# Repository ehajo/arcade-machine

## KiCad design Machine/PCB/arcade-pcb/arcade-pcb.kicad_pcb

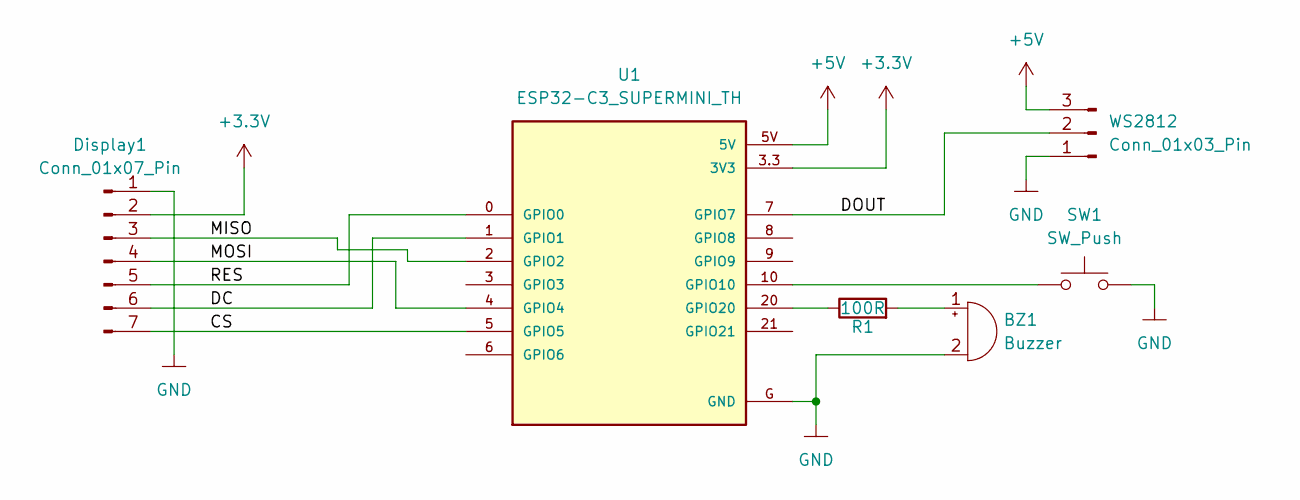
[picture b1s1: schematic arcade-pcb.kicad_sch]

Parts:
BZ1: Buzzer; Buzzer_12x9.5RM7.6
Display1: Conn_01x07_Pin; PinHeader_1x07_P1.27mm_Vertical_hand
R1: 100R; R_Axial_DIN0207_L6.3mm_D2.5mm_P7.62mm_Horizontal
SW1: SW_Push; SW_Tactile_SPST_Angled_PTS645Vx39-2LFS
U1: ESP32-C3_SUPERMINI_TH; MODULE_ESP32-C3_SUPERMINI_SMD
WS2812: Conn_01x03_Pin; PinHeader_1x03_P2.54mm_Vertical

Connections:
+3.3V: Display1.2, U1.3.3 (3V3)
+5V: U1.5V, WS2812.3
/CS: Display1.7, U1.5 (GPIO5)
/DC: Display1.6, U1.1 (GPIO1)
/DOUT: U1.7 (GPIO7), WS2812.2
/MISO: Display1.3, U1.2 (GPIO2)
/MOSI: Display1.4, U1.4 (GPIO4)
/RES: Display1.5, U1.0 (GPIO0)
GND: BZ1.2 (-), Display1.1, SW1.2, U1.G (GND), WS2812.1
unnamed: BZ1.1 (+), R1.2
unnamed: SW1.1, U1.10 (GPIO10)
unnamed: R1.1, U1.20 (GPIO20)

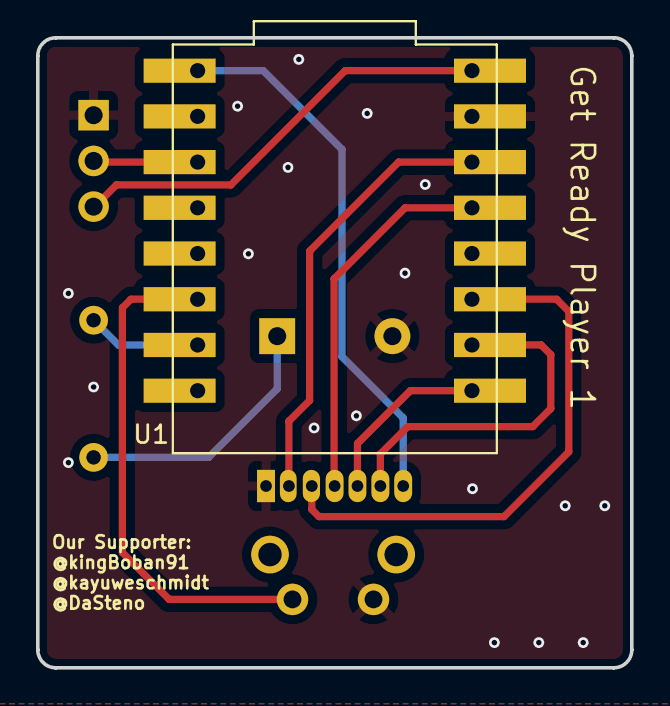
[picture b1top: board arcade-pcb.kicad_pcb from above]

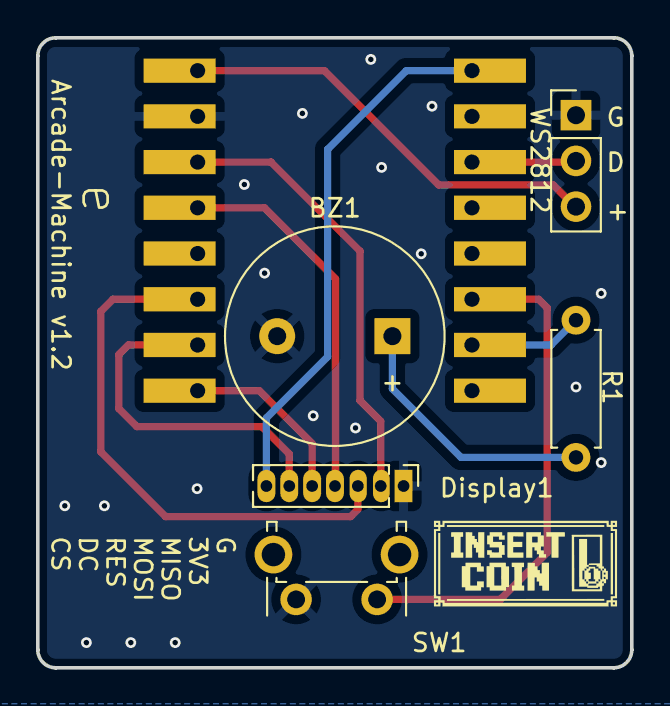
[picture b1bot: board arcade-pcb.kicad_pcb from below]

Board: 2 copper layers, 33.0 x 35.0 mm, 6 parts (5 on the bottom side), 12 nets.

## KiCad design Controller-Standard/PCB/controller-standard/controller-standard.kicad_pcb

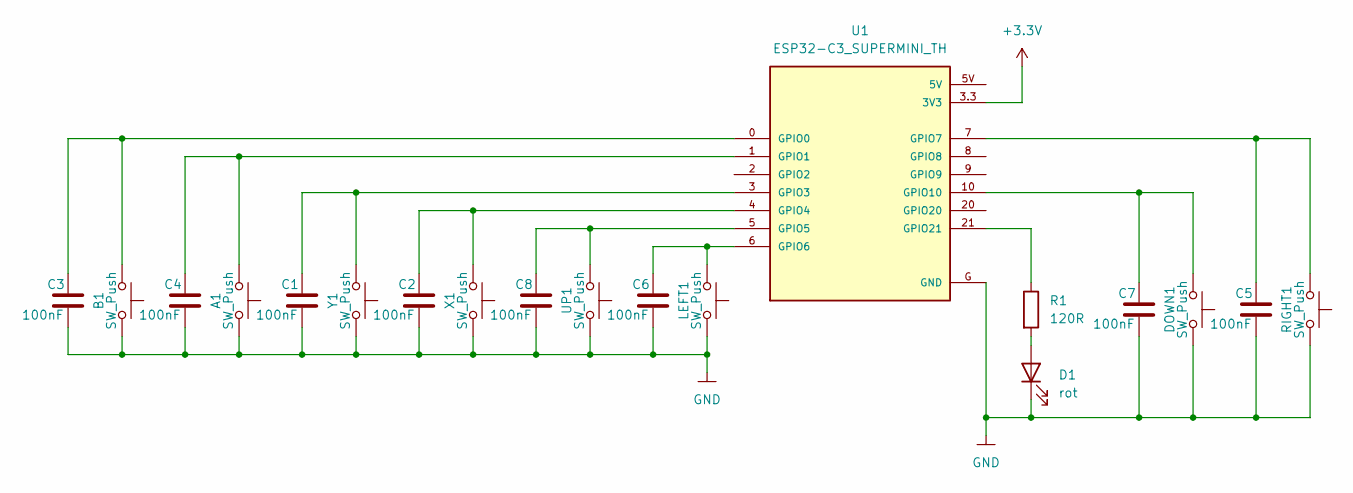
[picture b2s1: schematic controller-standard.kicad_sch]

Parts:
A1: SW_Push; SW_PUSH_6mm_H5mm
B1: SW_Push; SW_PUSH_6mm_H5mm
C1, C2, C3, C4, C5, C6, C7, C8: 100nF; C_0805_2012Metric_Pad1.18x1.45mm_HandSolder
D1: rot; LED_D3.0mm
DOWN1: SW_Push; SW_PUSH_6mm_H5mm
LEFT1: SW_Push; SW_PUSH_6mm_H5mm
R1: 120R; R_Axial_DIN0207_L6.3mm_D2.5mm_P7.62mm_Horizontal
RIGHT1: SW_Push; SW_PUSH_6mm_H5mm
U1: ESP32-C3_SUPERMINI_TH; MODULE_ESP32-C3_SUPERMINI_SMD
UP1: SW_Push; SW_PUSH_6mm_H5mm
X1: SW_Push; SW_PUSH_6mm_H5mm
Y1: SW_Push; SW_PUSH_6mm_H5mm

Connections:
+3.3V: U1.3.3 (3V3)
GND: A1.2, B1.2, C1.2, C2.2, C3.2, C4.2, C5.2, C6.2, C7.2, C8.2, D1.1 (K), DOWN1.2, LEFT1.2, RIGHT1.2, U1.G (GND), UP1.2, X1.2, Y1.2
unnamed: D1.2 (A), R1.2
unnamed: B1.1, C3.1, U1.0 (GPIO0)
unnamed: A1.1, C4.1, U1.1 (GPIO1)
unnamed: C1.1, U1.3 (GPIO3), Y1.1
unnamed: C2.1, U1.4 (GPIO4), X1.1
unnamed: C8.1, U1.5 (GPIO5), UP1.1
unnamed: C6.1, LEFT1.1, U1.6 (GPIO6)
unnamed: C5.1, RIGHT1.1, U1.7 (GPIO7)
unnamed: C7.1, DOWN1.1, U1.10 (GPIO10)
unnamed: R1.1, U1.21 (GPIO21)

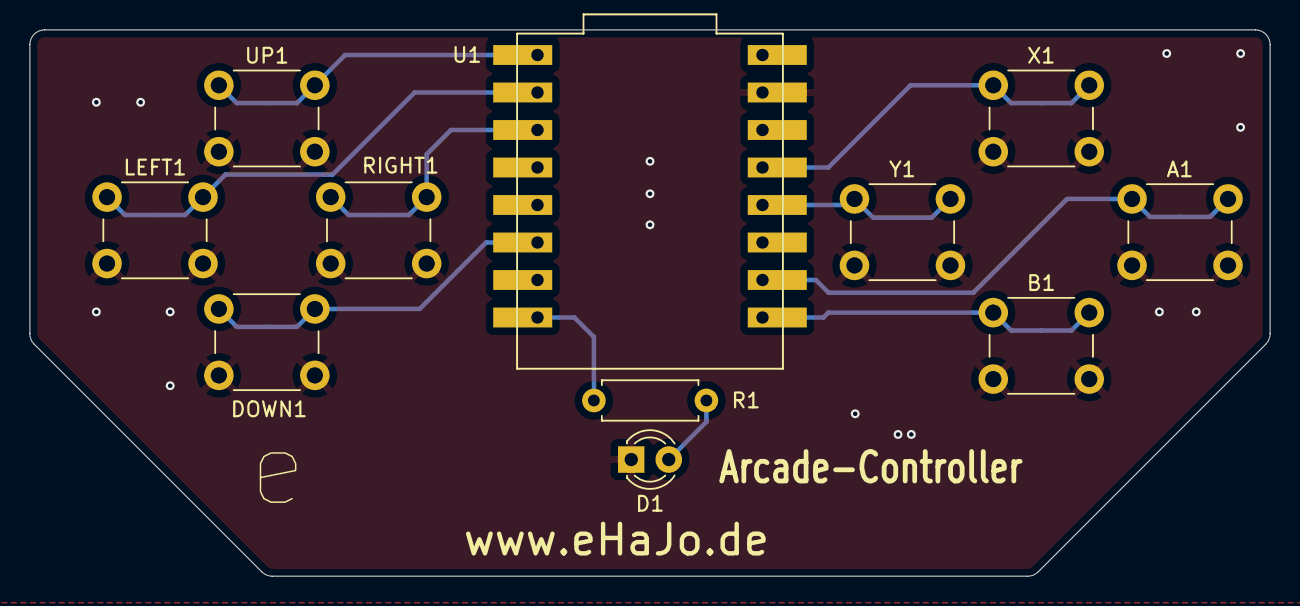
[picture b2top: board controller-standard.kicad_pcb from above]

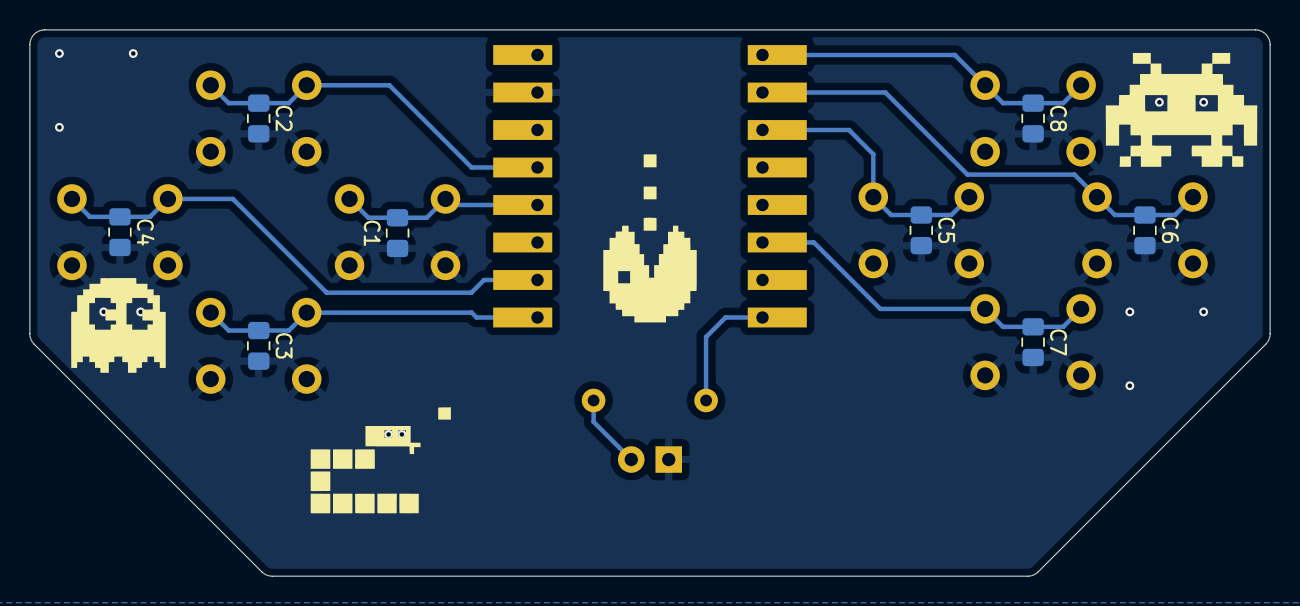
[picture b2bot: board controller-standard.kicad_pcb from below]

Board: 2 copper layers, 84.0 x 37.0 mm, 19 parts (8 on the bottom side), 11 nets.

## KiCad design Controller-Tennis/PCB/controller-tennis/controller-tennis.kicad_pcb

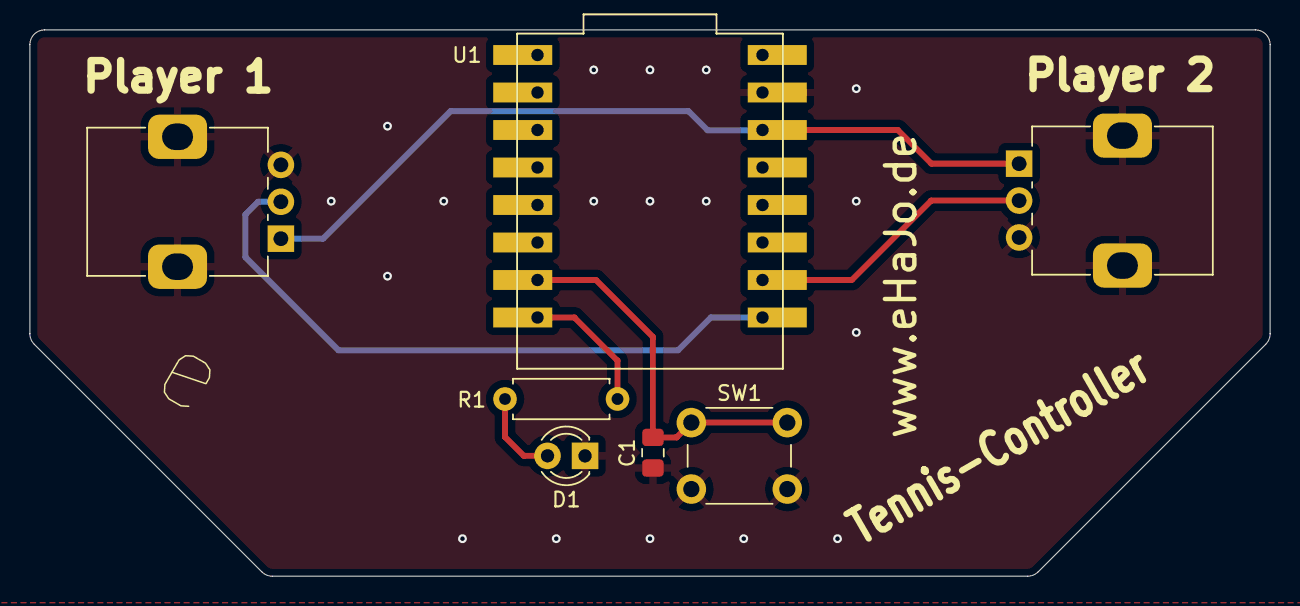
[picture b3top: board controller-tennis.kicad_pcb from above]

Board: 2 copper layers, 84.0 x 37.0 mm, 7 parts (0 on the bottom side), 7 nets.

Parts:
C1: 100nF; C_0805_2012Metric_Pad1.18x1.45mm_HandSolder
D1: rot; LED_D3.0mm
Player 1, Player 2: 10k; Potentiometer_Alps_RK09K_Single_Vertical
R1: 120R; R_Axial_DIN0207_L6.3mm_D2.5mm_P7.62mm_Horizontal
SW1: SW_Push; SW_PUSH_6mm
U1: ESP32-C3_SUPERMINI_TH; MODULE_ESP32-C3_SUPERMINI_SMD

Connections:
+3.3V: Player 1.1, Player 2.1, U1.3.3 (3V3)
GND: C1.2, D1.1 (K), Player 1.3, Player 1.MP (MountPin), Player 2.3, Player 2.MP (MountPin), SW1.2, U1.G (GND)
unnamed: D1.2 (A), R1.2
unnamed: Player 1.2, U1.0 (GPIO0)
unnamed: Player 2.2, U1.1 (GPIO1)
unnamed: C1.1, SW1.1, U1.20 (GPIO20)
unnamed: R1.1, U1.21 (GPIO21)

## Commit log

2026-03-03 status quo
    not working, all kap00t
2026-03-06 miracles!
    omg its working! thanks to kingboban and claude!
2026-03-06 alien attack
    dank claude funktioniert erschreckenderweise auch alien attack! krass.
2026-03-06 alien with sound
    jetzt sogar in farbe und bunt ach ne, nur mit sound!
2026-03-06 initial commit
    jetzt auch mit bauteilen statt aliens!
2026-05-15 aktueller stand
2026-05-20 Release tennis controller pairing v1.0
2026-05-21 Add ESP32-C3 release binaries
